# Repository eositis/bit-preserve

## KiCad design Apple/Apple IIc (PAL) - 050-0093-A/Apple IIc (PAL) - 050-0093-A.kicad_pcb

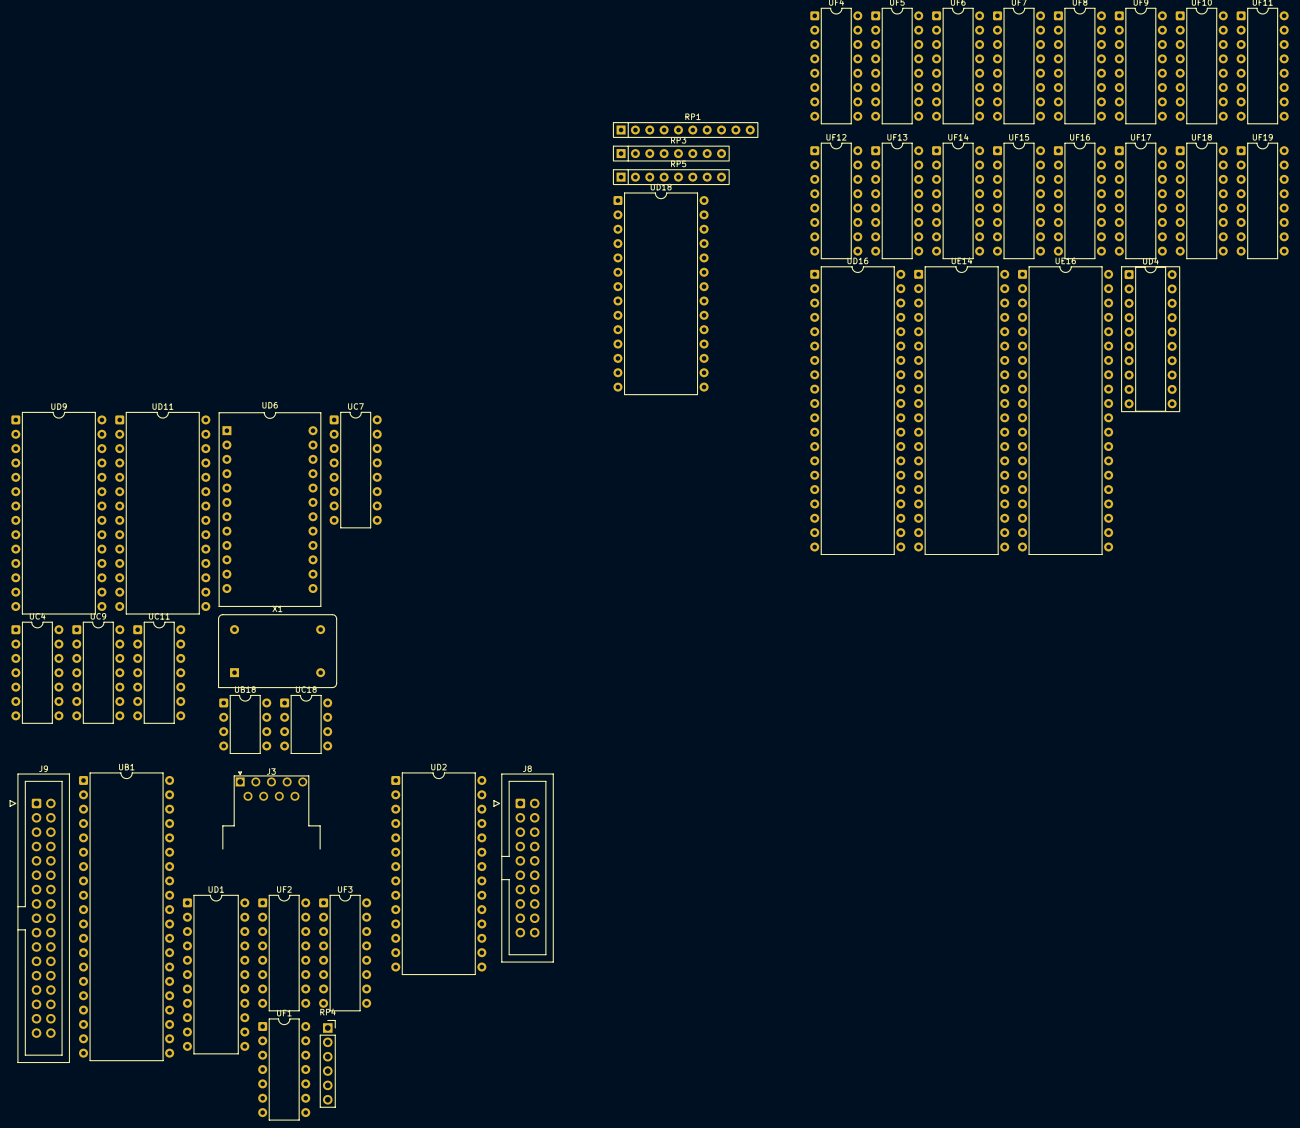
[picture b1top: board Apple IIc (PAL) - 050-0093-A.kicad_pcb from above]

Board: 2 copper layers, 44 parts (0 on the bottom side), 142 nets, no tracks yet.

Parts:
J3: Game; DSUB-9_Pins_Horizontal_P2.77x2.54mm_EdgePinOffset9.40mm
J8: Internal Disk; IDC-Header_2x10_P2.54mm_Vertical
J9: Keyboard; IDC-Header_2x17_P2.54mm_Vertical
RP1: 1k; R_Array_SIP10
RP3, RP5: 1k; R_Array_SIP8
RP4: 112-0315; PinSocket_1x06_P2.54mm_Vertical
UB1: 3600PRO; DIP-40_W15.24mm
UB18: LM311; DIP-8_W7.62mm
UC4: MC1489L; DIP-14_W7.62mm
UC7: 74LS161; DIP-16_W7.62mm
UC9: 74LS32; DIP-14_W7.62mm
UC11: MC1488L; DIP-14_W7.62mm
UC18: 555; DIP-8_W7.62mm
UD1: 2716; DIP-22_W10.16mm
UD2: IWM; DIP-28_W15.24mm
UD4: 16R8?; DIP-20_W7.62mm_Socket
UD6: GLU; DIP-24_18.0mmx34.29mm_W15.24mm
UD9, UD11: 6551; DIP-28_W15.24mm
UD16: 65c02; DIP-40_W15.24mm
UD18: 27c256; DIP-28_W15.24mm
UE14: IOU; DIP-40_W15.24mm
UE16: MMU; DIP-40_W15.24mm
UF1: NE556; DIP-14_W7.62mm
UF2: ILQ-1; DIP-16_W7.62mm
UF3: 74LS251; DIP-16_W7.62mm
UF4, UF5, UF6, UF7, UF8, UF9, UF10, UF11, UF12, UF13, UF14, UF15, UF16, UF17, UF18, UF19: MK4164N; DIP-16_W7.62mm
X1: OSC; Oscillator_DIP-14

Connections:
+5V: J3.2, J8.11, J8.12, J9.23, J9.25, RP1.1 (R1.1), RP4.1 (COM1), UB1.30 (VCC), UC4.14 (Vcc), UC9.14 (VCC), UC11.5 (InB2), UC11.9 (InC2), UC11.13 (InD1), UC11.14 (Vcc), UC18.8 (VCC), UD1.21 (VPP), UD2.26 (VCC), UD4.20 (+5V), UD6.24 (VCC), UD9.15 (VCC), UD11.15 (VCC), UD16.8 (VDD), UD18.1, UD18.28 (VCC), UE14.28 (+5V), UE16.15 (~INH), UE16.25 (+5V), UF1.4 (RESA), UF1.10 (RESB), UF1.14 (VCC), UF2.10, UF2.12, UF2.14, UF3.16 (VCC), UF12.8 (VCC), UF13.8 (VCC), UF14.8 (VCC), UF15.8 (VCC), UF16.8 (VCC), UF17.8 (VCC), UF18.8 (VCC), UF19.8 (VCC)
+12V: J8.13, J8.15, J8.17
-12V: J8.9, UB1.27 (VGG), UC11.1 (Vee)
/CPU MMU IOU RAM/A0: UD2.3 (A0), UD6.2 (A0), UD9.13 (RS0), UD11.13 (RS0), UD16.9 (A0), UD18.10 (A0), UE16.2 (A0), UF3.11 (S0)
/CPU MMU IOU RAM/A1: UD2.4 (A1), UD9.14 (RS1), UD11.14 (RS1), UD16.10 (A1), UD18.9 (A1), UE16.40 (A1), UF3.10 (S1)
/CPU MMU IOU RAM/A2: UD2.5 (A2), UD16.11 (A2), UD18.8 (A2), UE16.39 (A2), UF3.9 (S2)
/CPU MMU IOU RAM/A3: UD2.6 (A3), UD6.3 (A3), UD16.12 (A3), UD18.7 (A3), UE16.38 (A3)
/CPU MMU IOU RAM/A4: UD6.4 (A4), UD9.2 (CS0), UD11.2 (CS0), UD16.13 (A4), UD18.6 (A4), UE16.37 (A4)
/CPU MMU IOU RAM/A5: UD6.5 (A5), UD16.14 (A5), UD18.5 (A5), UE16.36 (A5)
/CPU MMU IOU RAM/A6: UD6.6 (A6), UD16.15 (A6), UD18.4 (A6), UE14.29 (A6), UE16.35 (A6)
/CPU MMU IOU RAM/A7: UD6.7 (A7), UD16.16 (A7), UD18.3 (A7), UE16.34 (A7)
/CPU MMU IOU RAM/A8: UD16.17 (A8), UD18.25 (A8), UE16.33 (A8)
/CPU MMU IOU RAM/A9: UD16.18 (A9), UD18.24 (A9), UE16.32 (A9)
/CPU MMU IOU RAM/A10: UD16.19 (A10), UD18.21 (A10), UE16.31 (A10)
/CPU MMU IOU RAM/A11: UD16.20 (A11), UD18.23 (A11), UE16.30 (A11)
/CPU MMU IOU RAM/A12: UD16.22 (A12), UD18.2 (A12), UE16.29 (A12)
/CPU MMU IOU RAM/A13: UD16.23 (A13), UD18.26 (A13), UE16.28 (A13)
/CPU MMU IOU RAM/A14: UD16.24 (A14), UE16.27 (A14)
/CPU MMU IOU RAM/A15: UD16.25 (A15), UE16.26 (A15)
/CPU MMU IOU RAM/AKD: UB1.5 (AKD), UE14.31 (AKD)
/CPU MMU IOU RAM/D0: UD1.9 (O1), UD2.10 (D0), UD9.18 (DB0), UD11.18 (DB0), UD16.33 (D0), UD18.11 (D0), UF18.2 (DIN), UF18.14 (DOUT)
/CPU MMU IOU RAM/D1: UD1.10 (O2), UD2.11 (D1), UD9.19 (DB1), UD11.19 (DB1), UD16.32 (D1), UD18.12 (D1), UF16.2 (DIN), UF16.14 (DOUT)
/CPU MMU IOU RAM/D2: UD1.11 (O3), UD2.12 (D2), UD9.20 (DB2), UD11.20 (DB2), UD16.31 (D2), UD18.13 (D2), UF17.2 (DIN), UF17.14 (DOUT)
/CPU MMU IOU RAM/D3: UD1.13 (O4), UD2.13 (D3), UD9.21 (DB3), UD11.21 (DB3), UD16.30 (D3), UD18.15 (D3), UF15.2 (DIN), UF15.14 (DOUT)
/CPU MMU IOU RAM/D4: UD1.14 (O5), UD2.15 (D4), UD9.22 (DB4), UD11.22 (DB4), UD16.29 (D4), UD18.16 (D4), UF14.2 (DIN), UF14.14 (DOUT)
/CPU MMU IOU RAM/D5: UD1.15 (O6), UD2.16 (D5), UD9.23 (DB5), UD11.23 (DB5), UD16.28 (D5), UD18.17 (D5), UF13.2 (DIN), UF13.14 (DOUT)
/CPU MMU IOU RAM/D6: UD1.16 (O7), UD2.17 (D6), UD9.24 (DB6), UD11.24 (DB6), UD16.27 (D6), UD18.18 (D6), UF12.2 (DIN), UF12.14 (DOUT)
/CPU MMU IOU RAM/D7: UD2.18 (D7), UD6.14 (D7), UD9.25 (DB7), UD11.25 (DB7), UD16.26 (D7), UD18.19 (D7), UE14.9 (MD7), UE16.21 (MD7), UF3.5 (Y), UF19.2 (DIN), UF19.14 (DOUT)
/CPU MMU IOU RAM/RA0: UE14.17 (RA0), UE16.6 (RA0), UF12.5 (A0), UF13.5 (A0), UF14.5 (A0), UF15.5 (A0), UF16.5 (A0), UF17.5 (A0), UF18.5 (A0), UF19.5 (A0)
/CPU MMU IOU RAM/RA1: UE14.18 (RA1), UE16.7 (RA1), UF12.7 (A1), UF13.7 (A1), UF14.7 (A1), UF15.7 (A1), UF16.7 (A1), UF17.7 (A1), UF18.7 (A1), UF19.7 (A1)
/CPU MMU IOU RAM/RA2: UE14.19 (RA2), UE16.8 (RA2), UF12.6 (A2), UF13.6 (A2), UF14.6 (A2), UF15.6 (A2), UF16.6 (A2), UF17.6 (A2), UF18.6 (A2), UF19.6 (A2)
/CPU MMU IOU RAM/RA3: UE14.20 (RA3), UE16.9 (RA3), UF12.12 (A3), UF13.12 (A3), UF14.12 (A3), UF15.12 (A3), UF16.12 (A3), UF17.12 (A3), UF18.12 (A3), UF19.12 (A3)
/CPU MMU IOU RAM/RA4: UE14.21 (RA4), UE16.10 (RA4), UF12.11 (A4), UF13.11 (A4), UF14.11 (A4), UF15.11 (A4), UF16.11 (A4), UF17.11 (A4), UF18.11 (A4), UF19.11 (A4)
/CPU MMU IOU RAM/RA5: UE14.22 (RA5), UE16.11 (RA5), UF12.10 (A5), UF13.10 (A5), UF14.10 (A5), UF15.10 (A5), UF16.10 (A5), UF17.10 (A5), UF18.10 (A5), UF19.10 (A5)
/CPU MMU IOU RAM/RA6: UE14.23 (RA6), UE16.12 (RA6), UF12.13 (A6), UF13.13 (A6), UF14.13 (A6), UF15.13 (A6), UF16.13 (A6), UF17.13 (A6), UF18.13 (A6), UF19.13 (A6)
/CPU MMU IOU RAM/RA7: UE14.24 (RA7), UE16.13 (RA7), UF12.9 (A7), UF13.9 (A7), UF14.9 (A7), UF15.9 (A7), UF16.9 (A7), UF17.9 (A7), UF18.9 (A7), UF19.9 (A7)
/CPU MMU IOU RAM/RA14: UD18.27 (A14), UE14.7 (CASSO)
/CPU MMU IOU RAM/RR/~W: UC9.6, UF12.3 (~WRITE), UF13.3 (~WRITE), UF14.3 (~WRITE), UF15.3 (~WRITE), UF16.3 (~WRITE), UF17.3 (~WRITE), UF18.3 (~WRITE), UF19.3 (~WRITE)
/CPU MMU IOU RAM/R/~W: UC9.1, UC9.5, UD6.15 (R/~W), UD9.28 (R/~W), UD11.28 (R/~W), UD16.34 (R/~W), UE14.14 (R/~W), UE16.14 (R/~W)
/CPU MMU IOU RAM/SEGB: UD4.6 (SEGB), UE14.4 (SEGB)
/CPU MMU IOU RAM/TEXT: UD4.7 (TEXT), UD6.16 (TEXT)
/CPU MMU IOU RAM/VIDD7: UD4.5 (VIDD7), UE14.33 (VIDD7)
/CPU MMU IOU RAM/~CAS: UF12.15 (~CAS), UF13.15 (~CAS), UF14.15 (~CAS), UF15.15 (~CAS), UF16.15 (~CAS), UF17.15 (~CAS), UF18.15 (~CAS), UF19.15 (~CAS)
/CPU MMU IOU RAM/~IOUSELIO: UC9.8, UE14.30 (~IOUSELIO)
/CPU MMU IOU RAM/~IRQ: RP1.3 (R2.2), UD9.26 (IRQ), UD11.26 (IRQ), UD16.4 (~IRQ), UE14.16 (~IRQ)
/CPU MMU IOU RAM/~RAS: UE14.35 (~RAS), UF12.4 (~RAS), UF13.4 (~RAS), UF14.4 (~RAS), UF15.4 (~RAS), UF16.4 (~RAS), UF17.4 (~RAS), UF18.4 (~RAS), UF19.4 (~RAS)
/CPU MMU IOU RAM/~RESET: J9.29, RP1.4 (R3.2), UD2.23 (~RESET), UD6.11 (RESET), UD9.4 (RES), UD11.4 (RES), UD16.40 (~RES), UE14.15 (~RESET)
/CPU MMU IOU RAM/~ROMEN: RP1.8 (R7.2), UD18.20 (~CE)
/CPU MMU IOU RAM/~ROMOE: RP5.3 (R2.2), UD18.22 (~OE)
/IWM/DISKACTY: J8.19, J9.11
/IWM/RDDATA: J8.16, UD2.21 (SENSE)
/IWM/SEEKPH0: J8.2, UD2.1 (PH0)
/IWM/SEEKPH1: J8.4, UD2.28 (PH1)
/IWM/SEEKPH2: J8.6, UD2.2 (PH2)
/IWM/SEEKPH3: J8.8, UD2.27 (PH3)
/IWM/WRDATA: J8.18, UD2.8 (WDAT)
/IWM/WRPROT: J8.20, UD2.22 (RD)
/IWM/~DR1: J8.14, UD2.20 (~EN1)
/IWM/~WRREQ: J8.10, UD2.9 (~WREQ)
/Keyboard_and_Gameport/80COLSW: J9.19, UF3.4 (I0)
/Keyboard_and_Gameport/CAPL: J9.16, UF2.9, UF3.3 (I1)
/Keyboard_and_Gameport/CAPS: J9.28, RP1.5 (R4.2), UD1.22 (A9)
/Keyboard_and_Gameport/CONTROL: J9.32, RP1.7 (R6.2), UB1.28 (~CNTL)
/Keyboard_and_Gameport/CP0: RP1.9 (R8.2), UF1.5 (OA), UF3.15 (I4)
/Keyboard_and_Gameport/CP1: RP1.10 (R9.2), UF1.9 (OB), UF3.14 (I5)
/Keyboard_and_Gameport/FLASH: J9.27, UC18.3 (Q)
/Keyboard_and_Gameport/GAMESW0: J3.7, RP4.2 (R3), UF2.2, UF2.3
/Keyboard_and_Gameport/GAMESW1: J3.1, RP4.4 (R4), UF2.6, UF2.7
/Keyboard_and_Gameport/KSTRB: UB1.16 (KSTRD), UD9.17 (DSR), UE14.32 (KSTRB)
/Keyboard_and_Gameport/LANGSW: J9.15, RP3.5 (R4.2), UD1.19 (A10)
/Keyboard_and_Gameport/OAPL: J9.26, UF2.13, UF3.2 (I2)
/Keyboard_and_Gameport/PDL0/XMOVE: J3.5, UE14.13 (PDL0/XMOVE)
/Keyboard_and_Gameport/PDL1/YDIR: J3.8, UF3.12 (I7)
/Keyboard_and_Gameport/SHIFT: J9.34, RP1.6 (R5.2), UB1.29 (~SHFT)
/Keyboard_and_Gameport/X0: J9.12, UB1.40 (X0)
/Keyboard_and_Gameport/X1: J9.33, UB1.39 (X1)
/Keyboard_and_Gameport/X2: J9.18, UB1.38 (X2)
/Keyboard_and_Gameport/X3: J9.20, UB1.37 (X3)
/Keyboard_and_Gameport/X4: J9.3, UB1.36 (X4)
/Keyboard_and_Gameport/X5: J9.5, UB1.35 (X5)
/Keyboard_and_Gameport/X6: J9.7, UB1.34 (X6)
/Keyboard_and_Gameport/X7: J9.9, UB1.33 (X7)
/Keyboard_and_Gameport/XDIR: J3.4, UF3.13 (I6)
/Keyboard_and_Gameport/Y0: J9.31, UB1.17 (Y0)
/Keyboard_and_Gameport/Y1: J9.24, UB1.18 (Y1)
/Keyboard_and_Gameport/Y2: J9.22, UB1.19 (Y2)
/Keyboard_and_Gameport/Y3: J9.8, UB1.20 (Y3)
/Keyboard_and_Gameport/Y4: J9.14, UB1.21 (Y4)
/Keyboard_and_Gameport/Y5: J9.6, UB1.22 (Y5)
/Keyboard_and_Gameport/Y6: J9.10, UB1.23 (Y6)
/Keyboard_and_Gameport/Y7: J9.1, UB1.24 (Y7)
/Keyboard_and_Gameport/Y8: J9.4, UB1.25 (Y8)
/Keyboard_and_Gameport/Y9: J9.2, UB1.26 (Y9)
/Keyboard_and_Gameport/YMOVE: J3.9, UE14.10 (YMOVE)
/Keyboard_and_Gameport/~C06X: UE16.16 (~C06X), UF3.7 (~OE)
/Keyboard_and_Gameport/~C07X: UE16.22 (~C07X), UF1.6 (TRIGA), UF1.8 (TRIGB)
/Keyboard_and_Gameport/~KBD: UD1.20 (~OE), UE16.18 (~KBD)
/Serial and GLU/7M: UD2.24 (FCLK), UD4.2 (7M), UD6.20 (7M)
/Serial and GLU/14M: UC7.2 (CP), UD4.1 (14M), UD6.1 (14M)
/Serial and GLU/BCLK: UC7.12 (Q2), UD9.6 (XTAL1), UD11.6 (XTAL1)
/Serial and GLU/CREF: UD4.3 (CREF), UD6.19 (CREF)
/Serial and GLU/GR: UD6.10 (GR), UE14.2 (GR)
/Serial and GLU/PH0: UD4.15 (PH0), UD6.8 (PH0), UD9.27 (PH2), UD11.27 (PH2), UD16.37 (ϕ0), UE14.26 (PH0), UE16.3 (PH0)
/Serial and GLU/PH1: UC9.4, UD4.14 (PH1)
/Serial and GLU/~CLKEN: RP3.2 (R1.2), X1.1 (CLKEN)
/Serial and GLU/~DISK: UD2.7 (~DEV), UD6.21 (DISK)
/Serial and GLU/~EN80: UC9.2, UE16.17 (~EN80)
/Serial and GLU/~GLUEN: RP3.6 (R5.2), UD6.13 (GLUEN)
/Serial and GLU/~SELIO: UC9.9, UD6.9 (SELIO), UE16.24 (~SELIO)
/Serial and GLU/~SER: UD6.23 (SER), UD9.3 (CS1), UD11.3 (CS1)
/Video/Q3: UD2.25 (Q3), UD4.16 (Q3), UE14.27 (Q3), UE16.4 (Q3)
GND: J3.3, J8.1, J8.3, J8.5, J8.7, J9.21, RP3.1 (R1.1), RP4.6 (COM2), UB1.15 (VDD), UB18.1 (GND), UB18.4 (V-), UC4.7 (GND), UC7.8 (GND), UC9.7 (GND), UC11.7 (GND), UC18.1 (GND), UD1.12 (GND), UD2.14 (GND), UD4.10 (GND), UD6.12 (GND), UD9.1 (GND), UD9.9 (CTS), UD11.1 (GND), UD11.9 (CTS), UD16.1 (~VP), UD16.21 (VSS), UD18.14 (GND), UE14.1 (GND), UE16.1 (GND), UF1.7 (GND), UF2.15, UF3.8 (GND), UF12.16 (VSS), UF13.16 (VSS), UF14.16 (VSS), UF15.16 (VSS), UF16.16 (VSS), UF17.16 (VSS), UF18.16 (VSS), UF19.16 (VSS)
unnamed: RP3.4 (R3.2), UD4.11 (~TMGEN)
unnamed: RP4.5 (R1), UF2.5, UF2.8
unnamed: RP4.3 (R2), UF2.1, UF2.4
unnamed: UB1.13 (B2), UD1.7 (KA1)
unnamed: UB1.12 (B3), UD1.8 (KA0)
unnamed: UB1.11 (B4), UD1.1 (KA7)
unnamed: UB1.10 (B5), UD1.2 (KA6)
unnamed: UB1.9 (B6), UD1.3 (KA5)
unnamed: UB1.8 (B7), UD1.4 (KA4)
unnamed: UB1.7 (B8), UD1.5 (KA3)
unnamed: UB1.6 (B9), UD1.6 (KA2)
unnamed: UC4.3 (OutA), UD11.12 (RxD)
unnamed: UC4.6 (OutB), UD11.16 (DCD)
unnamed: UC4.8 (OutC), UD9.12 (RxD)
unnamed: UC4.11 (OutD), UD9.16 (DCD)
unnamed: UC11.2 (InA), UD11.10 (TxD)
unnamed: UC11.4 (InB1), UD11.8 (RTS)
unnamed: UC11.10 (InC1), UD9.10 (TxD)
unnamed: UC11.12 (InD2), UD9.8 (RTS)
unnamed: UB18.7, UC18.4 (R)
unnamed: UC18.2 (TR), UC18.6 (THR)
unnamed: UD4.4 (H0), UE14.40 (H0)
unnamed: UD4.9 (~80COL), UE14.6 (~80COL)
unnamed: UD4.8 (~CASEN), UE16.23 (~CASEN)
unnamed: UE14.25 (~PRAS), UE16.5 (~PRAS)
unnamed: UF1.3 (CTA), UF1.11 (CTB), UF2.11
unnamed: UF1.1 (DISA), UF1.2 (THRA)
unnamed: UF1.12 (THRB), UF1.13 (DISB)
unnamed: UF2.16, UF3.1 (I3)
S5: RP1.2 (R1.2), UC7.1 (~MR), UC7.7 (CEP), UC7.9 (~PE), UC7.16 (VCC), UD16.6 (~NMI)
